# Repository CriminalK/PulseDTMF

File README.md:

PulseDTMF
=========

Code and schematics for an MSP430 based Pulse to DTMF telephone converter

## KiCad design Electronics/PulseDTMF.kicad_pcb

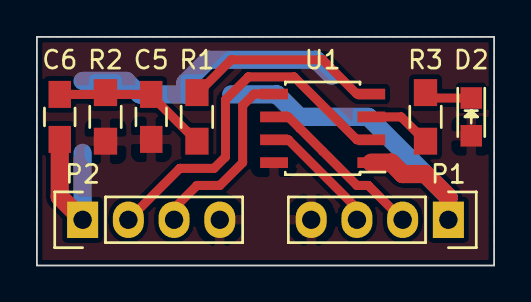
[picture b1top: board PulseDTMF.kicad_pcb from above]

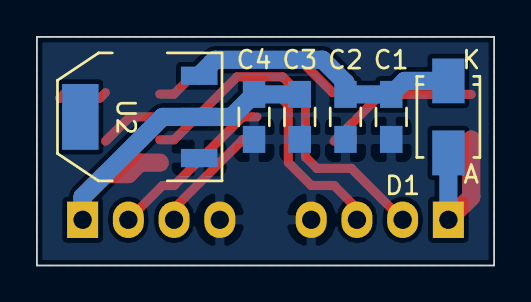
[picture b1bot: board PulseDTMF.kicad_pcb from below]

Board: 2 copper layers, 25.4 x 12.7 mm, 15 parts (6 on the bottom side), 12 nets.

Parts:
C1, C3, C6: 1uF; C_0805_HandSoldering
C2, C4, C5: 100nF; C_0805_HandSoldering
D1: D; SMA_Standard
D2: LED; LED-0805
P1, P2: CONN_01X04; Pin_Header_Straight_1x04
R1, R2, R3: 1K; R_0805_HandSoldering
U1: MSP430G2230ID; SOIC-8_3.9x4.9mm_Pitch1.27mm
U2: LD1117S33TR; SOT-223

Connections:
/DIAL1: P2.2, U1.2
/DIAL2: P2.3, U1.5
/LED: R3.2, U1.3
/LINE: C6.1, D1.2, P2.1
/SBWTCK: P1.3, U1.7
/SBWTDIO: P1.2, U1.6
/SIGNAL: R1.2, U1.4
GND: C1.2, C2.2, C3.2, C4.2, C5.1, D2.2, P1.4, P2.4, R2.1, U1.8, U2.1
unnamed: C1.1, C2.1, D1.1, U2.3
unnamed: C5.2, C6.2, R1.1, R2.2
unnamed: D2.1, R3.1
VDD: C3.1, C4.1, P1.1, U1.1, U2.2

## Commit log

2015-01-06 Added Eclipse project.
2015-01-09 Added KiCAD project and schematic.
2015-01-15 Added chips library; deleted backup files.
2015-11-27 New board.
2015-11-29 Changed PCB version with 25 thou signal traces, correct component references and correctly named GERBER files.
